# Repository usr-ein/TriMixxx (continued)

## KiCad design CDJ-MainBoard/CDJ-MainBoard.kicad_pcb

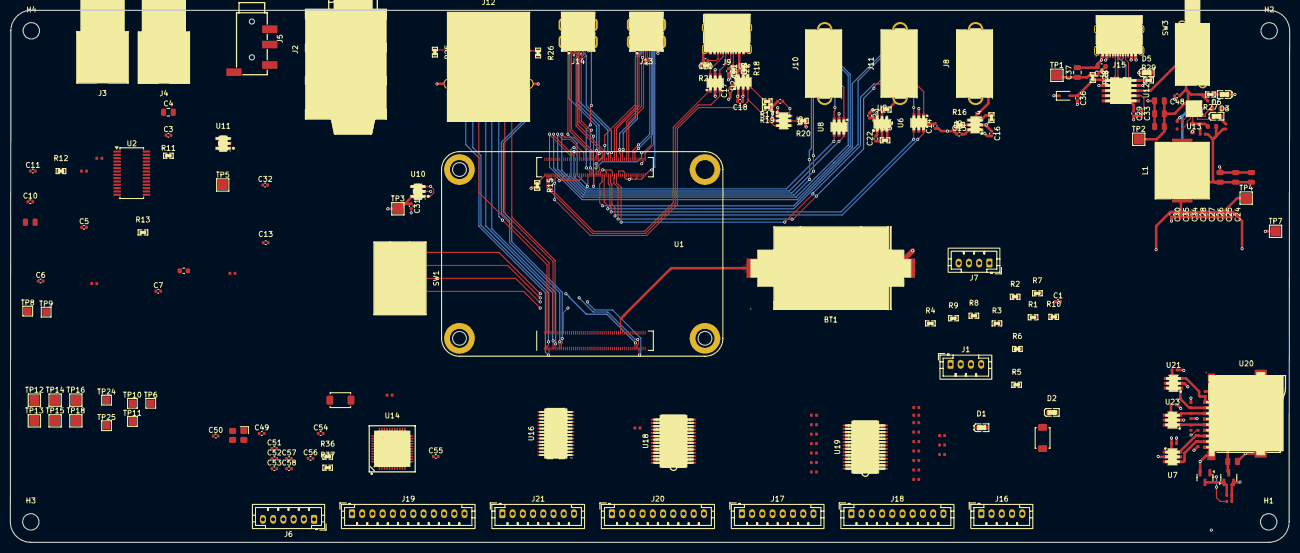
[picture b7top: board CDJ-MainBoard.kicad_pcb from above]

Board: 4 copper layers, 250.1 x 104.0 mm, 210 parts (0 on the bottom side), 219 nets.

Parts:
BT1: CR2032-BS-6-1; BAT-TH_CR2032-BS-6-1
C1, C3, C5, C10, C20, C21, C24, C27, C28, C29, C30, C33, C34, C35, C51, C53, C56, C57: 100nF; C_0402_1005Metric
C2, C8, C9, C12: 2.2uF; C_0402
C4: 10µF; C_0805_2012Metric
C6, C7, C14, C15, C16, C17, C18, C19, C22, C23, C36: 1µF; C_0402_1005Metric
C11, C13: 2.2nF; C_0402_1005Metric
C25, C26, C31, C32, C54, C55: 1uF; C_0402_1005Metric
C37: 10µF/35V; C_0805_2012Metric
C38: 100nF/50V; C_0603_1608Metric
C39, C40, C41, C46: 22uF; C_0805
C42, C43, C60, C76: 10uF; C_0805
C44, C61, C62, C63, C65, C66, C75: 100nF; C_0402
C45: 1uF; C_0402
C47: 100pF; C_0402
C48: 100nF/50V; C_0402_1005Metric
C49, C50: 15pF; C_0402_1005Metric
C52: 10nF; C_0402_1005Metric
C58: 22nF; C_0402_1005Metric
D1, D5: PSC-1608U52GC-G4; LED0603-RD_GREEN
D2: XL-1608UBC-04; LED0603-RD_BLUE
D3, D6: KT-0603R; LED0603-RD
D4: BZT52C3V3S; D_SOD-323
FB1: FB_0603
H1, H2, H3, H4: MountingHole; MountingHole_3.2mm_M3
J1: J_FAN_PWM; JST_PH_B4B-PH-K_1x04_P2.00mm_Vertical
J2: PJ-611E 6.35mm jack; AUDIO-TH_PJ-611E_1
J3: J_RCA_L (white); CONN-TH_AV-5
J4: J_RCA_R (red); CONN-TH_AV-5
J5: PJ-320D 3.5mm jack; AUDIO-SMD_PJ-320D-1
J6: J_ISP_ATMEGA; JST_PH_B6B-PH-K_1x06_P2.00mm_Vertical
J7: J_I2C; JST_PH_B4B-PH-K_1x04_P2.00mm_Vertical
J8: AUX POWER USB_A; USB-3.0-A-TH_HC-ST-003-010-L15.0-J-K
J9: TYPE-C_16PIN_2MD(073); USB-C-SMD_TYPE-C-6PIN-2MD-073
J10: USB_DJ_STICK (USB3_A); USB-3.0-A-TH_HC-ST-003-010-L15.0-J-K
J11: USB_SCREEN (USB3_A); USB-3.0-A-TH_HC-ST-003-010-L15.0-J-K
J12: HR911130A; RJ45-TH_HR911130A
J13, J14: PI HDMI_0 (HDMI_D_1.4 micro); HDMI-SMD_HDMI-101S
J15: TYPE-C-31-M-12; USB-C_SMD-TYPE-C-31-M-12_1
J16: J_JOGWHEEL; JST_PH_B5B-PH-K_1x05_P2.00mm_Vertical
J17: J_HOTCUES; JST_PH_B8B-PH-K_1x08_P2.00mm_Vertical
J18: J_LEFT_CTRLS; JST_PH_B10B-PH-K_1x10_P2.00mm_Vertical
J19: J_RIGHT_CTRLS; JST_PH_B12B-PH-K_1x12_P2.00mm_Vertical
J20: J_TOP_LEFT; JST_PH_B10B-PH-K_1x10_P2.00mm_Vertical
J21: J_TOP_RIGHT; JST_PH_B8B-PH-K_1x08_P2.00mm_Vertical
L1: SL1040-2R2M; IND-SMD_SL1040-R47M
Q1: AO3400A NFET; Q_SOT-23
Q2: SI2301CDS-T1-GE3 P-FET; Q_SOT-23
R1, R15, R16, R18, R20, R24, R36: 10kΩ; R0402
R2, R3, R21, R22: 5.1kΩ; R0402
R4, R6: 220Ω; R0402
R5, R7, R9: 2.2kΩ; R0402
R8: 100Ω; R0402
R10, R27, R28: 3.3kΩ; R0402
R11: 47kΩ; R0402
R12, R13: 470Ω; R0402
R14, R17, R19, R23: 100kΩ; R0402
R25, R26: 270Ω; R0402
R29: 1kΩ; R0402
R30: 100kΩ; R_0402
R31: 18kΩ; R_0603
R32: 10Ω; R_0402
R33: 510Ω; R_0402
R34: 200kΩ; R_0603
R35: 27kΩ; R_0603
R37: 22kΩ; R0402
R41, R52, R55, R70, R71, R72, R73, R74, R75, R76: 10kΩ; R_0402
R53, R54: 4.7kΩ; R_0402
R56, R57, R58, R59, R60, R61, R62, R63, R64, R65, R66, R67, R68: 330Ω; R_0402
R69: 33Ω; R_0402
SW1: DSWB05LHGET; SW-TH_DSWB05LHGET
SW2: PWR_BUT_CM5; SW_TS-1088-AR02016
SW3: SW_MAIN_POWER; SW-TH_PS-22E05
SW4: RESET_BTN; SW_TS-1088-AR02016
TP1: TP_20V_USB_RAIL; TestPoint_Pad_2.0x2.0mm
TP2: TP_20V_USB; TestPoint_Pad_2.0x2.0mm
TP3: TP_3.3_DGTL; TestPoint_Pad_2.0x2.0mm
TP4: TP_5V; TestPoint_Pad_2.0x2.0mm
TP5: TP_3.3_ANALOG; TestPoint_Pad_2.0x2.0mm
TP6: TP_I2C_SDA; TestPoint_Pad_1.5x1.5mm
TP7: TP_GND; TestPoint_Pad_2.0x2.0mm
TP8: TP_I2C_SCL; TestPoint_Pad_1.5x1.5mm
TP9: TP_I2S_BCK; TestPoint_Pad_1.5x1.5mm
TP10: TP_I2S_LRCK; TestPoint_Pad_1.5x1.5mm
TP11: TP_I2S_DIN; TestPoint_Pad_1.5x1.5mm
TP12: PF7; TestPoint_Pad_2.0x2.0mm
TP13: PF6; TestPoint_Pad_2.0x2.0mm
TP14: PF5; TestPoint_Pad_2.0x2.0mm
TP15: PF4; TestPoint_Pad_2.0x2.0mm
TP16: PF1; TestPoint_Pad_2.0x2.0mm
TP18: PC7; TestPoint_Pad_2.0x2.0mm
TP24: I2C_SDA_ARDUINO; TestPoint_Pad_1.5x1.5mm
TP25: I2C_SCL_ARDUINO; TestPoint_Pad_1.5x1.5mm
U1: Compute_Module_5_Functional; CM5
U2: PCM5122PW; TSSOP-28_4.4x9.7mm_P0.65mm
U3, U4, U5, U9: AP2553W6-7; SOT-26_L3.0-W1.6-P0.95-LS2.8-BL
U6, U7, U8, U21, U22, U23: USBLC6-2SC6-ES; SOT-23-6_L2.9-W1.6-P0.95-LS2.8-BR
U10: AP2112K-3.3 DIGITAL PSU LDO; SOT-23-5_L2.9-W1.6-P0.95-LS2.8-BR
U11: AP2112K-3.3 ANALOG AUDIO LDO; SOT-23-5_L2.9-W1.6-P0.95-LS2.8-BR
U12: CH224K; ESSOP-10_L4.9-W3.9-P1.0-LS6.0-TL-EP
U13: SY8368AQQC; QFN-12_L3.0-W3.0-P0.45-TL-EP
U14: ATmega32U4-A (Arduino MIDI controller); VQFN-44_L7.0-W7.0-P0.50-BL-EP5.2
U16: 74HC4067PW,118; TSSOP-28_L9.8-W6.6-P0.65-BL
U18, U19: MCP23017T-E/SS; SSOP-28_L10.2-W5.3-P0.65-LS7.8-BL
U20: TF-15×15; TF-SMD_TF-15-15
X1: X322516MLB4SI; OSC-SMD_4P-L3.2-W2.5-BL

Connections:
+3.3V: C1.1, C3.2, C4.2, C31.1, C65.1, C66.1, C75.1, J7.4, J12.10, Q2.2 (S), R5.2, R7.2, R11.2, R25.2, R26.2, R70.1, R71.1, R72.1, R73.1, R74.1, R75.1, R76.1, TP3.1, U1.78 (GPIO_VREF), U2.28 (DVDD), U7.5 (VCC), U10.5 (VOUT), U21.5 (VCC), U23.5 (VCC)
+3.3V_ANALOG: C5.2, C32.1, FB1.2, TP5.1, U2.1 (CPVDD), U2.8 (AVDD), U11.5 (VOUT)
+5V: C14.2, C16.2, C18.2, C22.2, C24.1, C25.1, C26.1, C27.1, C28.1, C30.1, C34.1, C35.1, C39.2, C40.2, C41.2, C47.2, C55.2, C56.2, C57.2, C61.1, C62.1, C63.1, J1.2, J6.2, J13.19 (+5V), J14.19 (+5V), J16.4, J17.7, J18.9, J19.10, J20.9, J21.7, L1.1, R1.1, R33.1, R34.2, R36.2, R37.1, R52.2, R53.1, R54.1, R55.2, TP4.1, U1.77 (+5V), U1.79 (+5V), U1.81 (+5V), U1.83 (+5V), U1.85 (+5V), U1.87 (+5V), U3.1 (IN), U4.1 (IN), U5.1 (IN), U6.5 (VCC), U8.5 (VCC), U9.1 (IN), U10.1 (VIN), U10.3 (EN), U11.1 (VIN), U11.3 (EN), U14.2 (UVCC), U14.7 (VBUS), U14.14 (VCC), U14.24 (AVCC), U14.34 (VCC), U14.44 (AVCC), U16.24 (VCC), U18.9 (VDD), U19.9 (VDD), U19.15 (A0), U22.5 (VCC)
+20V_USB: C42.1, C43.1, C46.2, C48.1, R27.2, R30.1, SW3.1, TP2.1, U13.4 (IN), U13.5 (IN), U13.6 (IN)
+20V_USB_RAIL: C37.1, C38.1, J15.A4B9 (VBUS), J15.B4A9 (VBUS), R28.1, TP1.1
/Arduino MIDI/BTN_BACK: J21.1, U19.7 (GPB6)
/Arduino MIDI/BTN_CUE: J18.2, U18.22 (GPA1)
/Arduino MIDI/BTN_DIRECTION: J20.1, U18.2 (GPB1)
/Arduino MIDI/BTN_HOTCUE_1: J17.1, U18.3 (GPB2)
/Arduino MIDI/BTN_HOTCUE_2: J17.2, U18.4 (GPB3)
/Arduino MIDI/BTN_HOTCUE_3: J17.3, U18.5 (GPB4)
/Arduino MIDI/BTN_JOG_MODE: J19.4, U19.21 (GPA0)
/Arduino MIDI/BTN_LOOP_IN: J20.2, U18.6 (GPB5)
/Arduino MIDI/BTN_LOOP_OUT: J20.3, U18.7 (GPB6)
/Arduino MIDI/BTN_MTEMPO: J19.2, U18.24 (GPA3)
/Arduino MIDI/BTN_PLAY: J18.1, U18.21 (GPA0)
/Arduino MIDI/BTN_RELOOP: J20.4, U18.8 (GPB7)
/Arduino MIDI/BTN_SEARCH_L: J18.3, U18.26 (GPA5)
/Arduino MIDI/BTN_SEARCH_R: J18.4, U18.27 (GPA6)
/Arduino MIDI/BTN_TEMPO_RANGE: J19.3, U18.25 (GPA4)
/Arduino MIDI/BTN_TEMPO_RST: J19.1, U18.23 (GPA2)
/Arduino MIDI/BTN_TRACK_L: J18.5, U18.28 (GPA7)
/Arduino MIDI/BTN_TRACK_R: J18.6, U18.1 (GPB0)
/Arduino MIDI/FADER_ADIN: J19.9, U16.9 (Y0)
/Arduino MIDI/I2C_SCL_ATMEGA: R53.2, TP25.1, U14.18 (PD0), U18.12 (SCK), U19.12 (SCK)
/Arduino MIDI/I2C_SDA_ATMEGA: R54.2, TP24.1, U14.19 (PD1), U18.13 (SDA), U19.13 (SDA)
/Arduino MIDI/JOG1: J16.1, U14.8 (PB0)
/Arduino MIDI/JOG_TOUCH: C58.1, J16.3, R37.2, U14.1 (PE6)
/Arduino MIDI/LED_CUE: J18.8, R61.2
/Arduino MIDI/LED_DIRECTION: J20.5, R59.2
/Arduino MIDI/LED_HOTCUE1: J17.4, R58.2
/Arduino MIDI/LED_HOTCUE2: J17.5, R57.2
/Arduino MIDI/LED_HOTCUE3: J17.6, R56.2
/Arduino MIDI/LED_JOG_MODE_1: J19.5, R66.1
/Arduino MIDI/LED_JOG_MODE_2: J19.6, R67.1
/Arduino MIDI/LED_LOOP_IN: J20.6, R63.1
/Arduino MIDI/LED_LOOP_OUT: J20.7, R64.1
/Arduino MIDI/LED_MTEMPO: J19.8, R60.2
/Arduino MIDI/LED_PLAY: J18.7, R62.2
/Arduino MIDI/LED_RELOOP: J20.8, R65.1
/Arduino MIDI/LED_TEMPO_RST: J19.7, R68.1
/Arduino MIDI/MCP1_INT: U14.28 (PB4), U18.19 (INTB), U18.20 (INTA)
/Arduino MIDI/MCP2_INT: U14.29 (PB5), U19.19 (INTB), U19.20 (INTA)
/Arduino MIDI/MUX_S0: U14.25 (PD4), U16.10 (S0)
/Arduino MIDI/MUX_S1: U14.26 (PD6), U16.11 (S1)
/Arduino MIDI/MUX_S2: U14.27 (PD7), U16.14 (S2)
/Arduino MIDI/MUX_S3: U14.22 (PD5), U16.13 (S3)
/Arduino MIDI/MUX_SIG: U14.41 (PF0), U16.1 (Z)
/Arduino MIDI/RELEASE_BRAKE_ADIN: J21.6, U16.7 (Y2)
/Arduino MIDI/TOUCH_BRAKE_ADIN: J21.5, U16.8 (Y1)
/Arduino MIDI/TRACK_ENC_A: J21.2, U14.30 (PB6)
/Arduino MIDI/TRACK_ENC_B: J21.3, U14.31 (PC6)
/Arduino MIDI/TRACK_ENC_PUSH: J21.4, U14.12 (PB7)
/Audio Outputs/RCA_LEFT: C13.1, J2.6 (LEFT_P), J3.2 (SIGNL), J5.2 (LEFT_P), R13.2
/Audio Outputs/RCA_RIGHT: C11.1, J2.4 (RIGHT_P), J4.2 (SIGNL), J5.3 (RIGHT_P), R12.2
/Compute Module/SD_CLK: R69.2, U20.5 (CLK), U23.1 (I/O1), U23.6 (I/O1)
/Compute Module/SD_CMD: R70.2, U1.62 (SD_CMD), U20.3 (CMD), U23.3 (I/O2), U23.4 (I/O2)
/Compute Module/SD_DAT0: R76.2, U1.63 (SD_DAT0), U7.1 (I/O1), U7.6 (I/O1), U20.7 (DAT0)
/Compute Module/SD_DAT1: R75.2, U1.67 (SD_DAT1), U7.3 (I/O2), U7.4 (I/O2), U20.8 (DAT1)
/Compute Module/SD_DAT2: R74.2, U1.69 (SD_DAT2), U20.1 (DAT2), U21.3 (I/O2), U21.4 (I/O2)
/Compute Module/SD_DAT3: R72.2, U1.61 (SD_DAT3), U20.2 (CD/DAT3), U21.1 (I/O1), U21.6 (I/O1)
/Compute Module/SD_PWR_ON: Q1.1 (G), R71.2, U1.75 (SD_PWR_ON)
/Compute Module/SD_VDD: C76.2, Q2.3 (D), U20.4 (VDD)
/Compute Module/S_BOOT_GND: SW1.3 (A3), U1.93 (~nRPIBOOT)
/Compute Module/S_BT_GND: SW1.2 (A2), U1.91 (~BT_nDisable)
/Compute Module/S_EEPROM_WP_GND: SW1.4 (A4), U1.20 (EEPROM_nWP)
/Compute Module/S_WIFI_GND: SW1.1 (A1), U1.89 (~WL_nDisable)
/HDMI and Ethernet/eth_nled_2: J12.13, U1.17 (~Ethernet_nLED2)
/HDMI and Ethernet/eth_nled_3: J12.12, U1.15 (~Ethernet_nLED3)
/HDMI and Ethernet/eth_p0_n: J12.3 (MDI0-), U1.10 (Ethernet_Pair0_N)
/HDMI and Ethernet/eth_p0_p: J12.2 (MDI0+), U1.12 (Ethernet_Pair0_P)
/HDMI and Ethernet/eth_p1_n: J12.7 (MDI1-), U1.6 (Ethernet_Pair1_N)
/HDMI and Ethernet/eth_p1_p: J12.4 (MDI1+), U1.4 (Ethernet_Pair1_P)
/HDMI and Ethernet/eth_p2_n: J12.6 (MDI2-), U1.9 (Ethernet_Pair2_N)
/HDMI and Ethernet/eth_p2_p: J12.5 (MDI2+), U1.11 (Ethernet_Pair2_P)
/HDMI and Ethernet/eth_p3_n: J12.9 (MDI3-), U1.5 (Ethernet_Pair3_N)
/HDMI and Ethernet/eth_p3_p: J12.8 (MDI3+), U1.3 (Ethernet_Pair3_P)
/USB DJ Ports/USB_AUX_POWR_VBUS: C15.2, J8.1 (VBUS), U3.6 (OUT)
/USB DJ Ports/USB_C_DJ_DM: U1.103 (USB_N), U22.3 (I/O2)
/USB DJ Ports/USB_C_DJ_DP: U1.105 (USB_P), U22.1 (I/O1)
/USB DJ Ports/USB_C_DJ_VBUS: C17.2, J9.2 (VBUS), J9.11 (VBUS), U4.6 (OUT)
/USB DJ Ports/USB_DJ_DM: U1.136 (USB3-0-DM), U8.6 (I/O1)
/USB DJ Ports/USB_DJ_DP: U1.134 (USB3-0-DP), U8.4 (I/O2)
/USB DJ Ports/USB_DJ_SSRXM: J10.5 (SSRX-), U1.128 (USB3-0-RX_N)
/USB DJ Ports/USB_DJ_SSRXP: J10.6 (SSRX+), U1.130 (USB3-0-RX_P)
/USB DJ Ports/USB_DJ_SSTXM: J10.8 (SSTX-), U1.140 (USB3-0-TX_N)
/USB DJ Ports/USB_DJ_SSTXP: J10.9 (SSTX+), U1.142 (USB3-0-TX_P)
/USB DJ Ports/USB_DJ_VBUS: C19.2, J10.1 (VBUS), U5.6 (OUT)
/USB DJ Ports/USB_DJ_VBUS_EN: R17.2, R19.2, U1.111 (VBUS_EN), U4.3 (EN), U5.3 (EN)
/USB DJ Ports/USB_SCR_DM: U1.165 (USB3-1-DM), U6.6 (I/O1)
/USB DJ Ports/USB_SCR_DP: U1.163 (USB3-1-DP), U6.4 (I/O2)
/USB DJ Ports/USB_SCR_SSRXM: J11.5 (SSRX-), U1.157 (USB3-1-RX_N)
/USB DJ Ports/USB_SCR_SSRXP: J11.6 (SSRX+), U1.159 (USB3-1-RX_P)
/USB DJ Ports/USB_SCR_SSTXM: J11.8 (SSTX-), U1.169 (USB3-1-TX_N)
/USB DJ Ports/USB_SCR_SSTXP: J11.9 (SSTX+), U1.171 (USB3-1-TX_P)
/USB DJ Ports/USB_SCR_VBUS: C23.2, J11.1 (VBUS), U9.6 (OUT)
GND: BT1.2, C1.2, C2.1, C3.1, C4.1, C5.1, C6.2, C7.2, C10.2, C11.2, C13.2, C14.1, C15.1, C16.1, C17.1, C18.1, C19.1, C20.2, C21.2, C22.1, C23.1, C24.2, C25.2, C26.2, C27.2, C28.2, C29.2, C30.2, C31.2, C32.2, C33.2, C34.2, C35.2, C36.2, C37.2, C38.2, C39.1, C40.1, C41.1, C42.2, C43.2, C45.1, C46.1, C48.2, C49.2, C50.1, C51.1, C53.1, C54.2, C55.1, C56.1, C57.1, C58.2, C60.2, C61.2, C62.2, C63.2, C65.2, C66.2, C75.2, C76.1, D1.1 (K), D2.1 (K), D3.1 (K), D4.1, D5.1 (K), J1.1, J2.2 (GND/SHLD), J5.1 (GND/SHLD), J6.6, J7.1, J8.4 (GND), J8.5 (Shield), J9.1 (GND), J9.12 (GND), J9.13 (SHELL), J9.14 (SHELL), J10.4 (GND), J10.7 (DRAIN), J10.10 (SHIELD), J11.4 (GND), J11.7 (DRAIN), J11.10 (SHIELD), J12.SHIELD0, J12.SHIELD1, J13.4 (D2S), J13.7 (D1S), J13.10 (D0S), J13.13 (CKS), J13.16 (GND), J14.4 (D2S), J14.7 (D1S), J14.10 (D0S), J14.13 (CKS), J14.16 (GND), J15.1 (EH), J15.2 (EH), J15.3 (EH), J15.4 (EH), J15.A1B12 (GND), J15.B1A12 (GND), J16.5, J17.8, J18.10, J19.11, J19.12, J20.10, J21.8, Q1.2 (S), R2.1, R3.1, R10.1, R14.1, R15.2, R16.1, R17.1, R18.1, R19.1, R20.1, R21.2, R22.2, R23.1, R24.1, R31.2, R35.2, R41.2, SW1.6 (B5), SW1.7 (B4), SW1.8 (B3), SW1.9 (B2), SW1.10 (B1), SW2.2, SW4.1, TP7.1, U1.1 (GND[51]), U1.2 (GND[51]), U1.7 (GND[51]), U1.8 (GND[51]), U1.13 (GND[51]), U1.14 (GND[51]), U1.22 (GND[51]), U1.23 (GND[51]), U1.32 (GND[51]), U1.33 (GND[51]), U1.42 (GND[51]), U1.43 (GND[51]), U1.52 (GND[51]), U1.53 (GND[51]), U1.59 (GND[51]), U1.60 (GND[51]), U1.65 (GND[51]), U1.66 (GND[51]), U1.71 (GND[51]), U1.74 (GND[51]), U1.98 (GND[51]), U1.107 (GND[51]), U1.108 (GND[51]), U1.113 (GND[51]), U1.114 (GND[51]), U1.119 (GND[51]), U1.120 (GND[51]), U1.125 (GND[51]), U1.126 (GND[51]), U1.131 (GND[51]), U1.132 (GND[51]), U1.137 (GND[51]), U1.138 (GND[51]), U1.144 (GND[51]), U1.150 (GND[51]), U1.155 (GND[51]), U1.156 (GND[51]), U1.161 (GND[51]), U1.162 (GND[51]), U1.167 (GND[51]), U1.168 (GND[51]), U1.173 (GND[51]), U1.174 (GND[51]), U1.179 (GND[51]), U1.180 (GND[51]), U1.185 (GND[51]), U1.186 (GND[51]), U1.191 (GND[51]), U1.192 (GND[51]), U1.197 (GND[51]), U1.198 (GND[51]), U2.3 (CPGND), U2.9 (AGND), U2.16 (ADR2/GPIO2/DOUT), U2.17 (MODE1), U2.18 (MODE2/MS), U2.20 (SCK), U2.24 (ADR1/MISO/FMT), U2.27 (DGND), U3.2 (GND), U4.2 (GND), U5.2 (GND), U6.2 (GND), U7.2 (GND), U8.2 (GND), U9.2 (GND), U10.2 (GND), U11.2 (GND), U12.2 (CFG2), U12.9 (CFG1), U12.11 (GND), U13.1 (GND), U13.3 (GND), U14.5 (UGND), U14.15 (GND), U14.23 (GND), U14.35 (GND), U14.43 (GND), U16.12 (GND), U16.15 (E#), U18.10 (VSS), U18.15 (A0), U18.16 (A1), U18.17 (A2), U19.10 (VSS), U19.16 (A1), U19.17 (A2), U20.6 (VSS), U20.10 (G3), U20.11 (G4), U20.12 (G1), U20.13 (G2), U21.2 (GND), U22.2 (GND), U23.2 (GND), X1.2 (GND), X1.4 (GND)
I2C_SCL: J7.3, R7.1, TP8.1, U1.80 (I2C_SCL0), U2.12 (SCL/MC/ATT1)
I2C_SDA: J7.2, R5.1, TP6.1, U1.82 (I2C_SDA0), U2.11 (SDA/MOSI/ATT2)
I2S_BCK: TP9.1, U1.49 (GPIO18), U2.21 (BCK)
I2S_DIN: TP11.1, U1.25 (GPIO21), U2.22 (DIN)
I2S_LRCLK: TP10.1, U1.26 (GPIO19), U2.23 (LRCK)
ISP_MISO: J6.1, U14.11 (PB3)
ISP_MOSI: J6.4, U14.10 (PB2)
ISP_RESET: C53.2, J6.3, R36.1, SW4.2, U14.13 (~RESET)
ISP_SCK: J6.5, J16.2, U14.9 (PB1)
unnamed: C2.2, FB1.1
unnamed: C9.1, R12.1
unnamed: C12.1, R13.1
unnamed: C47.1, R32.2
unnamed: C51.2, C52.1
unnamed: D1.2 (A), R4.1
unnamed: D2.2 (A), R6.2
unnamed: D3.2 (A), R27.1
unnamed: D5.2 (A), R29.2
unnamed: D6.2 (A), R33.2
unnamed: D6.1 (K), U13.11 (PG)
unnamed: J1.3, U1.16 (Fan_tacho)
unnamed: J1.4, U1.19 (Fan_PWM)
unnamed: C21.1, J9.4 (CC1), R22.1
unnamed: C20.1, J9.10 (CC2), R21.1
unnamed: J9.5 (DN2), J9.7 (DN1), U22.4 (I/O2)
unnamed: J9.6 (DP1), J9.8 (DP2), U22.6 (I/O1)
unnamed: J10.3 (D+), U8.3 (I/O2)
unnamed: J10.2 (D-), U8.1 (I/O1)
unnamed: J11.3 (D+), U6.3 (I/O2)
unnamed: J11.2 (D-), U6.1 (I/O1)
unnamed: J12.11, R26.1
unnamed: J12.14, R25.1
unnamed: J13.15 (CEC), U1.151 (HDMI0_CEC)
unnamed: J13.12 (CK+), U1.188 (HDMI0_CLK_P)
unnamed: J13.14 (CK-), U1.190 (HDMI0_CLK_N)
unnamed: J13.9 (D0+), U1.182 (HDMI0_TX0_P)
unnamed: J13.11 (D0-), U1.184 (HDMI0_TX0_N)
unnamed: J13.6 (D1+), U1.176 (HDMI0_TX1_P)
unnamed: J13.8 (D1-), U1.178 (HDMI0_TX1_N)
unnamed: J13.3 (D2+), U1.170 (HDMI0_TX2_P)
unnamed: J13.5 (D2-), U1.172 (HDMI0_TX2_N)
unnamed: J13.1 (HPD/HEAC-), U1.153 (HDMI0_HOTPLUG)
unnamed: J13.17 (SCL), U1.200 (HDMI0_SCL)
unnamed: J13.18 (SDA), U1.199 (HDMI0_SDA)
unnamed: J14.15 (CEC), U1.149 (HDMI1_CEC)
unnamed: J14.12 (CK+), U1.164 (HDMI1_CLK_P)
unnamed: J14.14 (CK-), U1.166 (HDMI1_CLK_N)
unnamed: J14.9 (D0+), U1.158 (HDMI1_TX0_P)
unnamed: J14.11 (D0-), U1.160 (HDMI1_TX0_N)
unnamed: J14.6 (D1+), U1.152 (HDMI1_TX1_P)
unnamed: J14.8 (D1-), U1.154 (HDMI1_TX1_N)
unnamed: J14.3 (D2+), U1.146 (HDMI1_TX2_P)
unnamed: J14.5 (D2-), U1.148 (HDMI1_TX2_N)
unnamed: J14.1 (HPD/HEAC-), U1.143 (HDMI1_HOTPLUG)
unnamed: J14.17 (SCL), U1.147 (HDMI1_SCL)
unnamed: J14.18 (SDA), U1.145 (HDMI1_SDA)
unnamed: C33.1, J15.A5 (CC1), U12.7 (CC1)
unnamed: C29.1, J15.B5 (CC2), U12.6 (CC2)
unnamed: J15.A7 (DN1), J15.B7 (DN2), U12.5 (DM)
unnamed: J15.A6 (DP1), J15.B6 (DP2), U12.4 (DP)
unnamed: Q1.3 (D), Q2.1 (G), R73.2
unnamed: R8.1, U1.55 (GPIO14)
unnamed: R9.1, R10.2, U1.51 (GPIO15)
unnamed: R15.1, U1.101 (USB_OTG_ID)
unnamed: R69.1, U1.57 (SD_CLK)
unnamed: R3.2, U1.94 (CC1)
unnamed: R2.2, U1.96 (CC2)
unnamed: R1.2, U1.99 (PMIC_ENABLE)
unnamed: SW2.1, U1.92 (PWR_Button)
unnamed: BT1.1, U1.76 (VBAT)
unnamed: R6.1, U1.95 (~PI_LED_nPWR)
unnamed: R4.2, U1.21 (~Pi_nLED_Activity)
unnamed: C8.1, U2.4 (CAPM)
unnamed: C8.2, U2.2 (CAPP)
unnamed: C10.1, C60.1, U2.26 (LDOO)
unnamed: C12.2, U2.6 (OUTL)
unnamed: C9.2, U2.7 (OUTR)
unnamed: C7.1, U2.10 (VCOM/DEMP)
unnamed: C6.1, U2.5 (VNEG)
unnamed: R11.1, U2.25 (XSMT)
unnamed: R14.2, U3.3 (EN)
unnamed: R16.2, U3.5 (ILIM)
unnamed: R18.2, U4.5 (ILIM)
unnamed: R20.2, U5.5 (ILIM)
unnamed: R23.2, U9.3 (EN)
unnamed: R24.2, U9.5 (ILIM)
unnamed: R29.1, U12.10 (PG)
unnamed: SW3.2, U12.8 (VBUS)
unnamed: C36.1, D4.2, R28.2, U12.1 (VDD)
unnamed: C44.2, U13.7 (BS)
unnamed: R30.2, R31.1, U13.12 (EN)
unnamed: R32.1, R34.1, R35.1, U13.9 (FB)
unnamed: C44.1, L1.2, U13.2 (LX)
unnamed: C45.2, U13.8 (VCC)
unnamed: C52.2, U14.42 (AREF)
unnamed: TP18.1, U14.32 (PC7)
unnamed: TP16.1, U14.40 (PF1)
unnamed: TP15.1, U14.39 (PF4)
unnamed: TP14.1, U14.38 (PF5)
unnamed: TP13.1, U14.37 (PF6)
unnamed: TP12.1, U14.36 (PF7)
unnamed: C54.1, U14.6 (UCAP)
unnamed: C50.2, U14.17 (XTAL1), X1.3 (OSC)
unnamed: C49.1, U14.16 (XTAL2), X1.1 (OSC)
unnamed: R41.1, U14.33 (~HWB/PE2)
unnamed: R52.1, U18.18 (RESET#)
unnamed: R62.1, U19.22 (GPA1)
unnamed: R61.1, U19.23 (GPA2)
unnamed: R60.1, U19.24 (GPA3)
unnamed: R59.1, U19.25 (GPA4)
unnamed: R58.1, U19.26 (GPA5)
unnamed: R57.1, U19.27 (GPA6)
unnamed: R56.1, U19.28 (GPA7)
unnamed: R63.2, U19.1 (GPB0)
unnamed: R64.2, U19.2 (GPB1)
unnamed: R65.2, U19.3 (GPB2)
unnamed: R66.2, U19.4 (GPB3)
unnamed: R67.2, U19.5 (GPB4)
unnamed: R68.2, U19.6 (GPB5)
unnamed: R55.1, U19.18 (RESET#)
UART_ATMEGA_RX: R8.2, U14.20 (PD2)
UART_ATMEGA_TX: R9.2, U14.21 (PD3)

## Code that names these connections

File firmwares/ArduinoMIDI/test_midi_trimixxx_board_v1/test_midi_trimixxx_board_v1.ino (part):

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 *     than that (see DEBOUNCE_SAMPLES) to avoid double-triggering.
 *   - LED channels are active-HIGH: MCP pin HIGH -> 2N7000 gate HIGH -> LED on.
 *   - Jogwheel touch (TCH) is active-LOW with the 22k pull-up on the JOGB PCB
 *     (pressed = LOW). PE6 (D7) set as plain INPUT, no internal pull-up.
 *   - Jog encoder uses the PJRC Encoder lib; D8/D9 aren't INT pins so the lib
 *     polls inside read() - fine for hand speed, may slip at full scratch.
 *
 * PIN MAP (Pro Micro / ATmega32U4)
 *   Tempo fader  ADIN -> A0 (PF7)      ADCT -> A1 (PF6)
 *   Jogwheel     TCH  -> D7  (PE6)     JOG1 -> D8 (PB4)   JOG2 -> D9 (PB5)
 *   I2C          SDA  -> D2 (PD1)      SCL  -> D3 (PD0)
 *   UART to Pi   RX1  -> D0 (PD2)      TX1  -> D1 (PD3)   (Serial1)
 *
 * MCP23017 channel map
 *   Inputs  (PORTA): GPA0 LOOP_START_BTN  GPA1 LOOP_END_BTN
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#define USB_BAUD        115200

// ---- Pro Micro pins
#define PIN_ADIN        A0        // PF7  tempo fader wiper (main channel)
#define PIN_ADCT        A1        // PF6  tempo calibration / control channel
#define PIN_TCH         7         // PE6  jogwheel touch
#define PIN_JOG1        8         // PB4  encoder A
#define PIN_JOG2        9         // PB5  encoder B

// ---- MCP23017 registers (IOCON.BANK = 0, the power-on default)
#define MCP_IODIRA      0x00
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unsigned long lastTick = 0;

// jog encoder (PJRC Encoder lib handles decoding; polls in read() on D8/D9)
Encoder jogWheel(PIN_JOG1, PIN_JOG2);

// ============================================================ MCP helpers ===
bool mcpWrite(uint8_t reg, uint8_t val) {
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    case T1_I2C:     runI2CTest();      break;   // one-shot, returns to menu
    case T2_FADER:   Serial.println(F("[Test 2] Move the fader. 'm' to stop.")); break;
    case T3_JOG:
      pinMode(PIN_TCH, INPUT);          // active-LOW; 22k pull-up lives on JOGB PCB
      jogWheel.write(0);                // zero the counter (lib already set D8/D9 pull-ups)
      Serial.println(F("[Test 3] Spin & touch the jog. 'm' to stop."));
      break;
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  static long shown = 0;
  static int lastTouch = -1;
  long pos = jogWheel.read();             // polls the encoder on D8/D9
  int touched = !digitalRead(PIN_TCH);    // active-LOW: pressed = 1
  if (first || pos != shown || touched != lastTouch) {
    first = false;
    shown = pos; lastTouch = touched;
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
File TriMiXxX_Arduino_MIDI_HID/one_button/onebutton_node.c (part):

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// Cut-through UART ring relay + 2x WS2812 + 1 button, ch32v003fun bare-metal.
//
// Ring:  S3(TX) -> node1.RX ; node1.TX -> node2.RX ; ... ; node50.TX -> S3(RX)
// Whole ring is 5V. USART1: RX = PD6 (DIN), TX = PD5 (DOUT). SWIO=PD1 (leave!).
//
// Every node runs the *identical* binary. Position in the chain is discovered
// at boot (ENUM frame), so there is no per-board config.
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
// ==== Pins matched to the OneButton board ==================================
#define BTN_PORT   GPIOC
#define BTN_PIN    1            // PC1: switch to GND, external 10k pull-up + 100nF (HW debounce)
#define WS_PORT    GPIOC
#define WS_PIN     0            // PC0: WS2812 data out (drives both LEDs in series)
// (bit-bang on purpose: PC0 is not an SPI MOSI pin, and refresh runs in the
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
// ---- independent watchdog: a hung node reboots itself instead of freezing
//      the whole downstream ring. LSI ~128kHz, /16 -> 8kHz, 0xFFF -> ~0.5s.
//      NOTE: comment iwdg_init() out while single-stepping over SWIO, or it
//      will reset the part whenever you pause at a breakpoint.
static void iwdg_init(void)
{
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    RCC->APB2PCENR |= RCC_APB2Periph_GPIOC | RCC_APB2Periph_GPIOD
                    | RCC_APB2Periph_USART1;

    // PD5 = USART1 TX : alt-function push-pull, 50 MHz  (nibble 0b1011)
    GPIOD->CFGLR &= ~(0xf << (4*5));
    GPIOD->CFGLR |=  (0xB << (4*5));
    // PD6 = USART1 RX : input with pull-up  (nibble 0b1000 + OUTDR bit)
    GPIOD->CFGLR &= ~(0xf << (4*6));
    GPIOD->CFGLR |=  (0x8 << (4*6));
    GPIOD->OUTDR |=  (1 << 6);

    // PC1 button: FLOATING input (nibble 0b0100). The external 10k + 100nF fully
    // define the level; an internal pull would just parallel the 10k and shorten
    // the debounce RC. So no pull, no OUTDR write for this pin.
    BTN_PORT->CFGLR &= ~(0xf << (4*BTN_PIN));
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
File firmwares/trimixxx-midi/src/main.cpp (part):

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// ---- Jog wheel (PCNT quad + touch) ----------------------------------------
#define JOG_A 6
#define JOG_B 7
#define JOG_TCH 11
// Touch is active-low (built in). Encoder needs no pull (OPIC drives it);
// set encoderPullup=true only as insurance against phantom counts if the
// jog cable is ever unplugged.
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// Wired inverted on this deck (high end = slow), so invert=true. Bench-measured
// offsets: top = -1944, bottom = +2150 (center tap is off electrical mid, hence
// the asymmetric per-side spans).
#define TEMPO_ADCT 8
#define TEMPO_ADIN 9
TempoFader tempo(TEMPO_ADCT, TEMPO_ADIN, /*spanToMax=*/1944, /*spanToMin=*/2150, /*invert=*/true);

// ---- Track encoder (KY-040 mechanical: CLK/DT/SW) --------------------------
#define ENC_CLK 33
#define ENC_DT 37
#define ENC_SW 38
TrackEncoder trackEnc(ENC_CLK, ENC_DT, ENC_SW);

// ---- Play/cue + loop boards (direct GPIO; pins baked into the drivers) ------
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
